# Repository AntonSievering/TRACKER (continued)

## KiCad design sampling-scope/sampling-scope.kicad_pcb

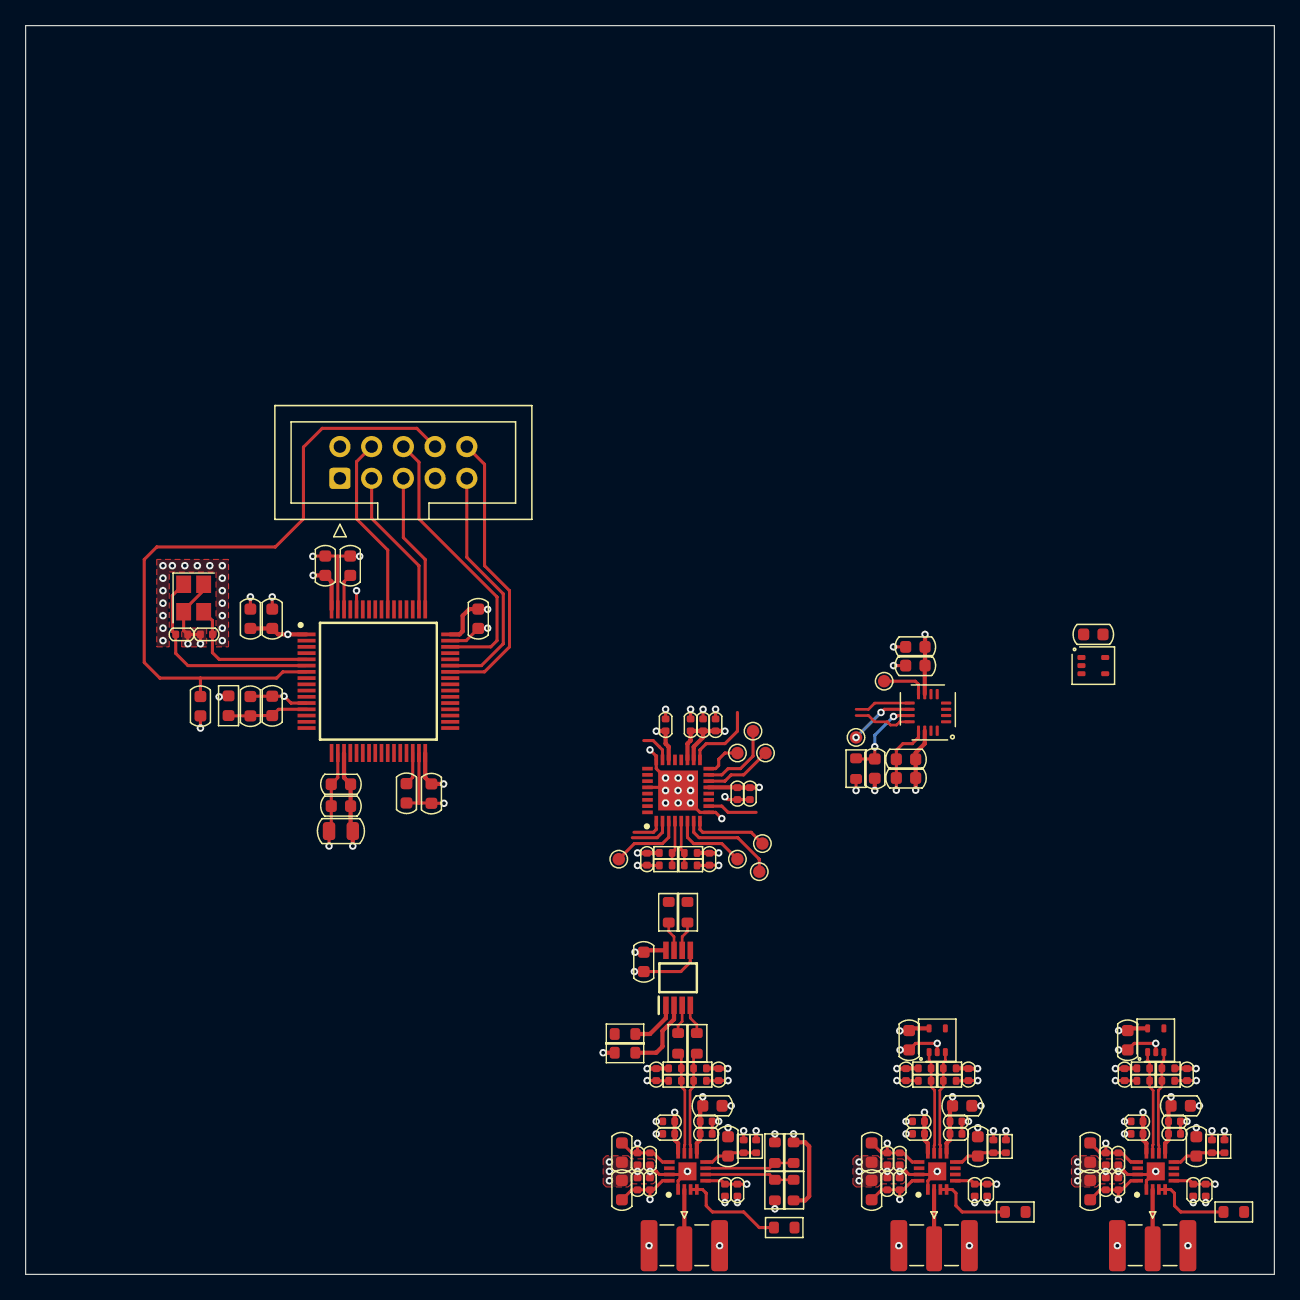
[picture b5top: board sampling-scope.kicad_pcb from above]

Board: 4 copper layers, 100.0 x 100.0 mm, 141 parts (0 on the bottom side), 53 nets.

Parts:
C1, C20, C21, C36, C37, C38, C39, C44, C45, C46, C47, C48, C49: 100n; C_0603_1608Metric
C2, C7, C8, C11, C12, C13, C14, C16, C18, C19, C24, C25, C26, C27, C29, C31, C32, C54, C55, C56, C57, C59, C61, C62, C63, C64, C65, C66, C67, C68, C69, C70, C71, C72, C73, C74, C75, C76, C77, C78: 100n; C_0402_1005Metric
C3, C4, C5, C6: 10n; C_0402_1005Metric
C9, C10, C15, C17, C22, C23, C28, C30, C43, C50, C51, C52, C53, C58, C60: 1u; C_0603_1608Metric
C33, C34, C35: 10n; C_0603_1608Metric
C40, C41: 2u2; C_0603_1608Metric
C42: 10u; C_0805_2012Metric
C79, C80: 10p; C_0402_1005Metric
FB1: 1k@100MHz; L_0603_1608Metric
IC1: SY89296UMG; QFN50P500X500X90-33N-D
IC2, IC4, IC6: ADCMP582; QFN50P300X300X80-17N-D
IC3: SY10EP51VKG; SOP65P490X110-8N
IC5: STM32H562RGT6; QFP50P1200X1200X160-64N
J1, J2, J3: SMA; SMA_Edge_Mount
J4: Conn_02x05_Counter_Clockwise; IDC-Header_2x05_P2.54mm_Vertical
R1, R3, R6, R8, R10, R21, R23, R25, R30, R32, R34: 127; R_0402_1005Metric
R2, R4, R7, R9, R11, R22, R24, R26, R31, R33, R35: 82.5; R_0402_1005Metric
R5, R14, R15, R16, R17, R18, R19, R20, R29, R37, R38: 0; R_0603_1608Metric
R27: 49R9; R_0603_1608Metric
R36: 470; R_0603_1608Metric
R39: 330; R_0603_1608Metric
TP1, TP4, TP5, TP6, TP7, TP8, TP9, TP10, TP11: TestPoint; TestPoint_Pad_D1.0mm
U1, U2, U4: LMV331; SOT-353_SC-70-5
U3: SY89831U; QFN-16_3x3mm_P0.5mm
X2: 40MHz; Crystal_SMD_Abracon_ABM8AIG-4Pin_3.2x2.5mm

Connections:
+3.3V: C1.1, C2.1, C3.1, C4.1, C5.1, C6.1, C7.1, C8.1, C15.1, C16.1, C18.1, C19.1, C20.1, C21.1, C28.1, C29.1, C31.1, C32.1, C33.1, C34.1, C35.1, C36.1, C37.1, C38.1, C42.1, C43.1, C44.1, C45.1, C46.1, C47.1, C48.1, C50.1, C58.1, C59.1, C61.1, C62.1, C69.1, C70.1, C71.1, C72.1, C73.1, C74.1, C75.1, C76.1, C77.1, C78.1, FB1.2, IC1.13 (VCC), IC1.18 (VCC), IC1.19 (VCC), IC1.22 (VCC), IC2.9 (V_{CCO}), IC2.12 (V_{CCO}), IC3.8 (VCC), IC4.9 (V_{CCO}), IC4.12 (V_{CCO}), IC5.1 (VBAT), IC5.19 (VDD_1), IC5.32 (VDD_2), IC5.48 (VDD_3), IC5.64 (VDD_4), IC6.9 (V_{CCO}), IC6.12 (V_{CCO}), R1.1, R3.1, R6.1, R8.1, R10.1, R15.1, R21.1, R23.1, R25.1, R30.1, R32.1, R34.1, R36.2, R38.2, U1.5 (V+), U2.5 (V+), U3.7 (VCC), U3.14 (VCC), U4.5 (V+)
+5VA: C10.1, C12.1, C14.1, C23.1, C25.1, C27.1, C53.1, C55.1, C57.1, C63.1, C64.1, C65.1, C66.1, C67.1, C68.1, IC2.5 (VCCI), IC2.16 (VCCI), IC4.5 (VCCI), IC4.16 (VCCI), IC6.5 (VCCI), IC6.16 (VCCI)
-5VA: C9.1, C11.1, C13.1, C22.1, C24.1, C26.1, C52.1, C54.1, C56.1, IC2.13 (V_{EE}), IC4.13 (V_{EE}), IC6.13 (V_{EE})
/Clock Fanout 1:4/IN+: IC1.20 (~Q), U3.12 (IN)
/Clock Fanout 1:4/IN-: IC1.21 (Q), U3.9 (~IN)
/Microcontroller/DEBUG_RX: IC5.43 (PA10), J4.9
/Microcontroller/DEBUG_TX: IC5.42 (PA9), J4.10
/Microcontroller/JTCK: IC5.49 (PA14), J4.5
/Microcontroller/JTDI: IC5.50 (PA15), J4.3
/Microcontroller/JTDO: IC5.55 (PB3), J4.4
/Microcontroller/JTMS: IC5.46 (PA13), J4.6
/Microcontroller/NRST: C39.1, IC5.7 (NRST), J4.8
/Microcontroller/OSC_IN: C79.2, IC5.5 (PH0-OSC_IN), X2.3
/Microcontroller/OSC_OUT: C80.2, IC5.6 (PH1-OSC_OUT), X2.1
/Microcontroller/stm32_vdda: C49.1, C51.1, FB1.1, IC5.13 (VDDA)
/Microcontroller/stm_vcap1: C40.1, IC5.30 (VCAP_1)
/Microcontroller/stm_vcap2: C41.1, IC5.62 (VCAP_2)
/Sampling Head CH1/High Speed Comparator/COMP_OUT+: IC4.11 (Q), R23.2, R24.1, U2.1 (+)
/Sampling Head CH1/High Speed Comparator/COMP_OUT-: IC4.10 (~Q), R25.2, R26.1, U2.3 (-)
/Sampling Head CH1/SIGNAL: IC4.2 (VP), J2.1 (In)
/Sampling Head CH2/High Speed Comparator/COMP_OUT+: IC6.11 (Q), R32.2, R33.1, U4.1 (+)
/Sampling Head CH2/High Speed Comparator/COMP_OUT-: IC6.10 (~Q), R34.2, R35.1, U4.3 (-)
/Sampling Head CH2/SIGNAL: IC6.2 (VP), J3.1 (In)
/Trigger Circuitry/High Speed Comparator/CMP_LE+: IC2.7 (LE), R36.1, R37.2
/Trigger Circuitry/High Speed Comparator/CMP_LE-: IC2.6 (~LE), R38.1, R39.2
/Trigger Circuitry/TRIG: IC2.2 (VP), J1.1 (In)
/Trigger Circuitry/comp_out+: IC2.11 (Q), R8.2, R9.1, R16.1
/Trigger Circuitry/comp_out-: IC2.10 (~Q), R10.2, R11.1, R17.1
/Trigger Circuitry/comp_out_r+: IC3.3 (CLK), R16.2
/Trigger Circuitry/comp_out_r-: IC3.4 (~CLK), R17.2
/Trigger Circuitry/dff_out+: IC3.7 (Q), R18.1
/Trigger Circuitry/dff_out-: IC3.6 (~Q), R19.1
/Trigger Circuitry/dff_out_r+: IC1.4 (IN), R1.2, R2.1, R18.2
/Trigger Circuitry/dff_out_r-: IC1.5 (~IN), R3.2, R4.1, R19.2
GND: C1.2, C2.2, C3.2, C4.2, C5.2, C6.2, C7.2, C8.2, C9.2, C10.2, C11.2, C12.2, C13.2, C14.2, C15.2, C16.2, C17.2, C18.2, C19.2, C20.2, C21.2, C22.2, C23.2, C24.2, C25.2, C26.2, C27.2, C28.2, C29.2, C30.2, C31.2, C32.2, C34.2, C35.2, C36.2, C37.2, C38.2, C39.2, C40.2, C41.2, C42.2, C43.2, C44.2, C45.2, C46.2, C47.2, C48.2, C49.2, C50.2, C51.2, C52.2, C53.2, C54.2, C55.2, C56.2, C57.2, C58.2, C59.2, C60.2, C61.2, C62.2, C63.2, C64.2, C65.2, C66.2, C67.2, C68.2, C69.2, C70.2, C71.2, C72.2, C73.2, C74.2, C75.2, C76.2, C77.2, C78.2, C79.1, C80.1, IC1.9 (GND), IC1.24 (GND), IC1.28 (GND), IC1.33 (EP), IC2.1 (VTP), IC2.15 (GND), IC2.17 (EP), IC3.5 (GND), IC4.1 (VTP), IC4.15 (GND), IC4.17 (EP), IC5.12 (VSSA), IC5.18 (VSS_1), IC5.31 (VSS_2), IC5.47 (VSS_3), IC5.60 (BOOT0), IC5.63 (VSS_4), IC6.1 (VTP), IC6.15 (GND), IC6.17 (EP), J1.2 (Ext), J2.2 (Ext), J3.2 (Ext), J4.2, J4.7, R2.2, R4.2, R7.2, R9.2, R11.2, R22.2, R24.2, R26.2, R27.2, R31.2, R33.2, R35.2, R37.1, R39.1, U1.2 (V-), U2.2 (V-), U3.13 (GND), U4.2 (V-), X2.2, X2.4
unnamed: IC1.15 (CASCADE), TP5.1
unnamed: IC1.3 (D10), TP1.1
unnamed: IC1.6 (VBB), TP9.1
unnamed: IC1.8 (VCF), TP7.1
unnamed: IC1.7 (VEF), TP8.1
unnamed: IC1.14 (~CASCADE), TP6.1
unnamed: IC1.16 (~EN), TP4.1
unnamed: IC2.3 (VN), IC2.4 (VTN), R5.2
unnamed: C17.1, IC2.8 (V_{TT}), R6.2, R7.1
unnamed: IC3.2 (D), R15.2
unnamed: IC3.1 (RESET), R14.2
unnamed: IC4.3 (VN), IC4.4 (VTN), R20.2
unnamed: C30.1, IC4.8 (V_{TT}), R21.2, R22.1
unnamed: IC6.3 (VN), IC6.4 (VTN), R29.2
unnamed: C60.1, IC6.8 (V_{TT}), R30.2, R31.1
unnamed: TP11.1, U3.8 (RESET)
unnamed: TP10.1, U3.10 (VREF-AC)
unnamed: C33.2, R27.1, U3.11 (VT)

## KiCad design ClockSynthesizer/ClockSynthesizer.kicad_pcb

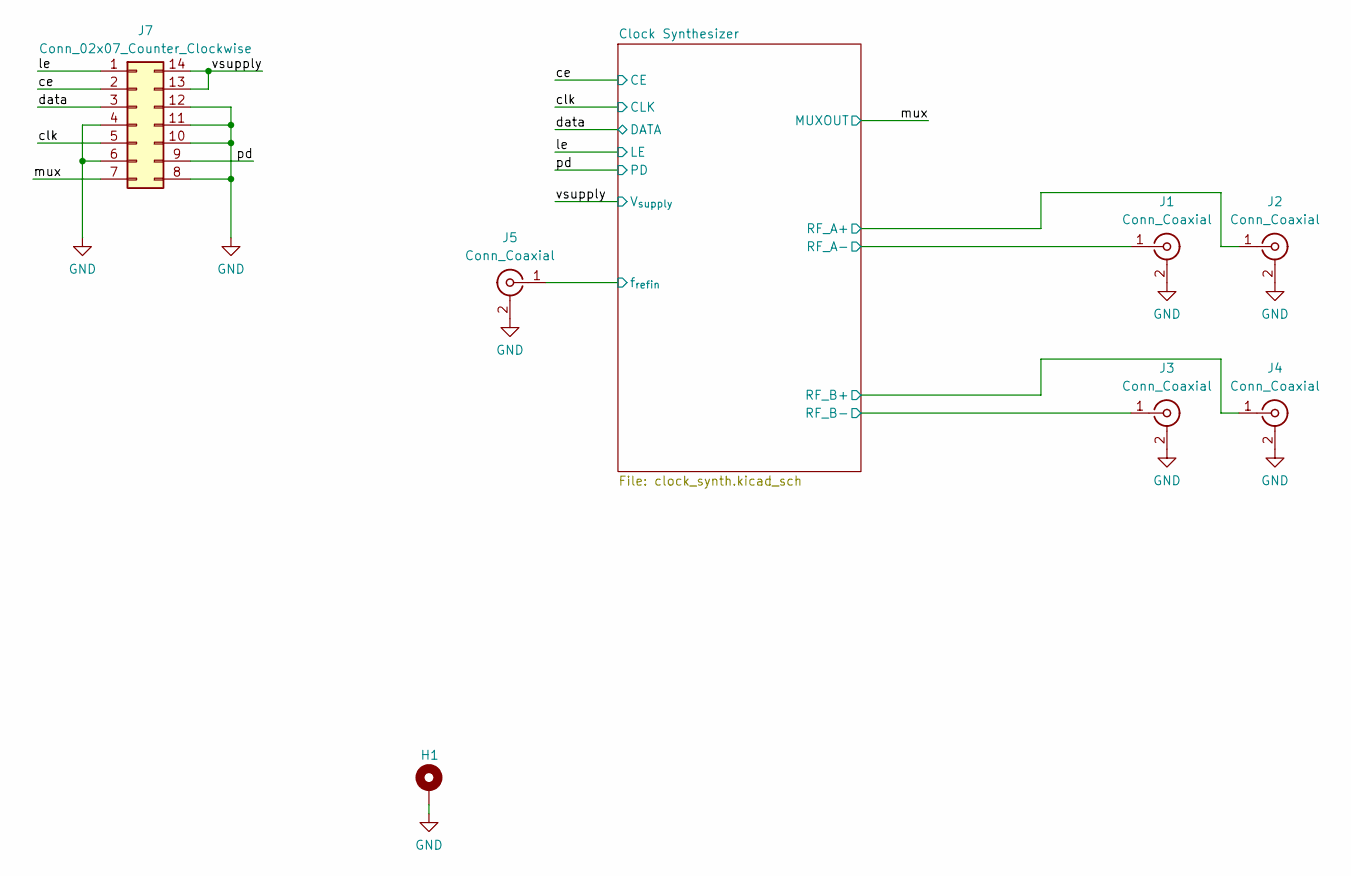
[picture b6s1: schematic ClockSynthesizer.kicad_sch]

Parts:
H1: MountingHole_Pad; MountingHole_3.2mm_M3_Pad_Via
J1, J2, J3, J4, J5: Conn_Coaxial; SMA_Amphenol_132289_EdgeMount
J7: Conn_02x07_Counter_Clockwise; PinHeader_2x07_P2.54mm_Horizontal

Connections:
+12V: J7.13, J7.14; also elsewhere on the board
/Clock Synthesizer/RF_A+: J2.1 (In); also elsewhere on the board
/Clock Synthesizer/RF_A-: J1.1 (In); also elsewhere on the board
/Clock Synthesizer/RF_B+: J4.1 (In); also elsewhere on the board
/Clock Synthesizer/RF_B-: J3.1 (In); also elsewhere on the board
/Clock Synthesizer/f_{refin}: J5.1 (In); also elsewhere on the board
/ce: J7.2; also elsewhere on the board
/clk: J7.5; also elsewhere on the board
/data: J7.3; also elsewhere on the board
/le: J7.1; also elsewhere on the board
/mux: J7.7; also elsewhere on the board
/pd: J7.9; also elsewhere on the board
GND: H1.1, J1.2 (Ext), J2.2 (Ext), J3.2 (Ext), J4.2 (Ext), J5.2 (Ext), J7.4, J7.6, J7.8, J7.10, J7.11, J7.12; also elsewhere on the board

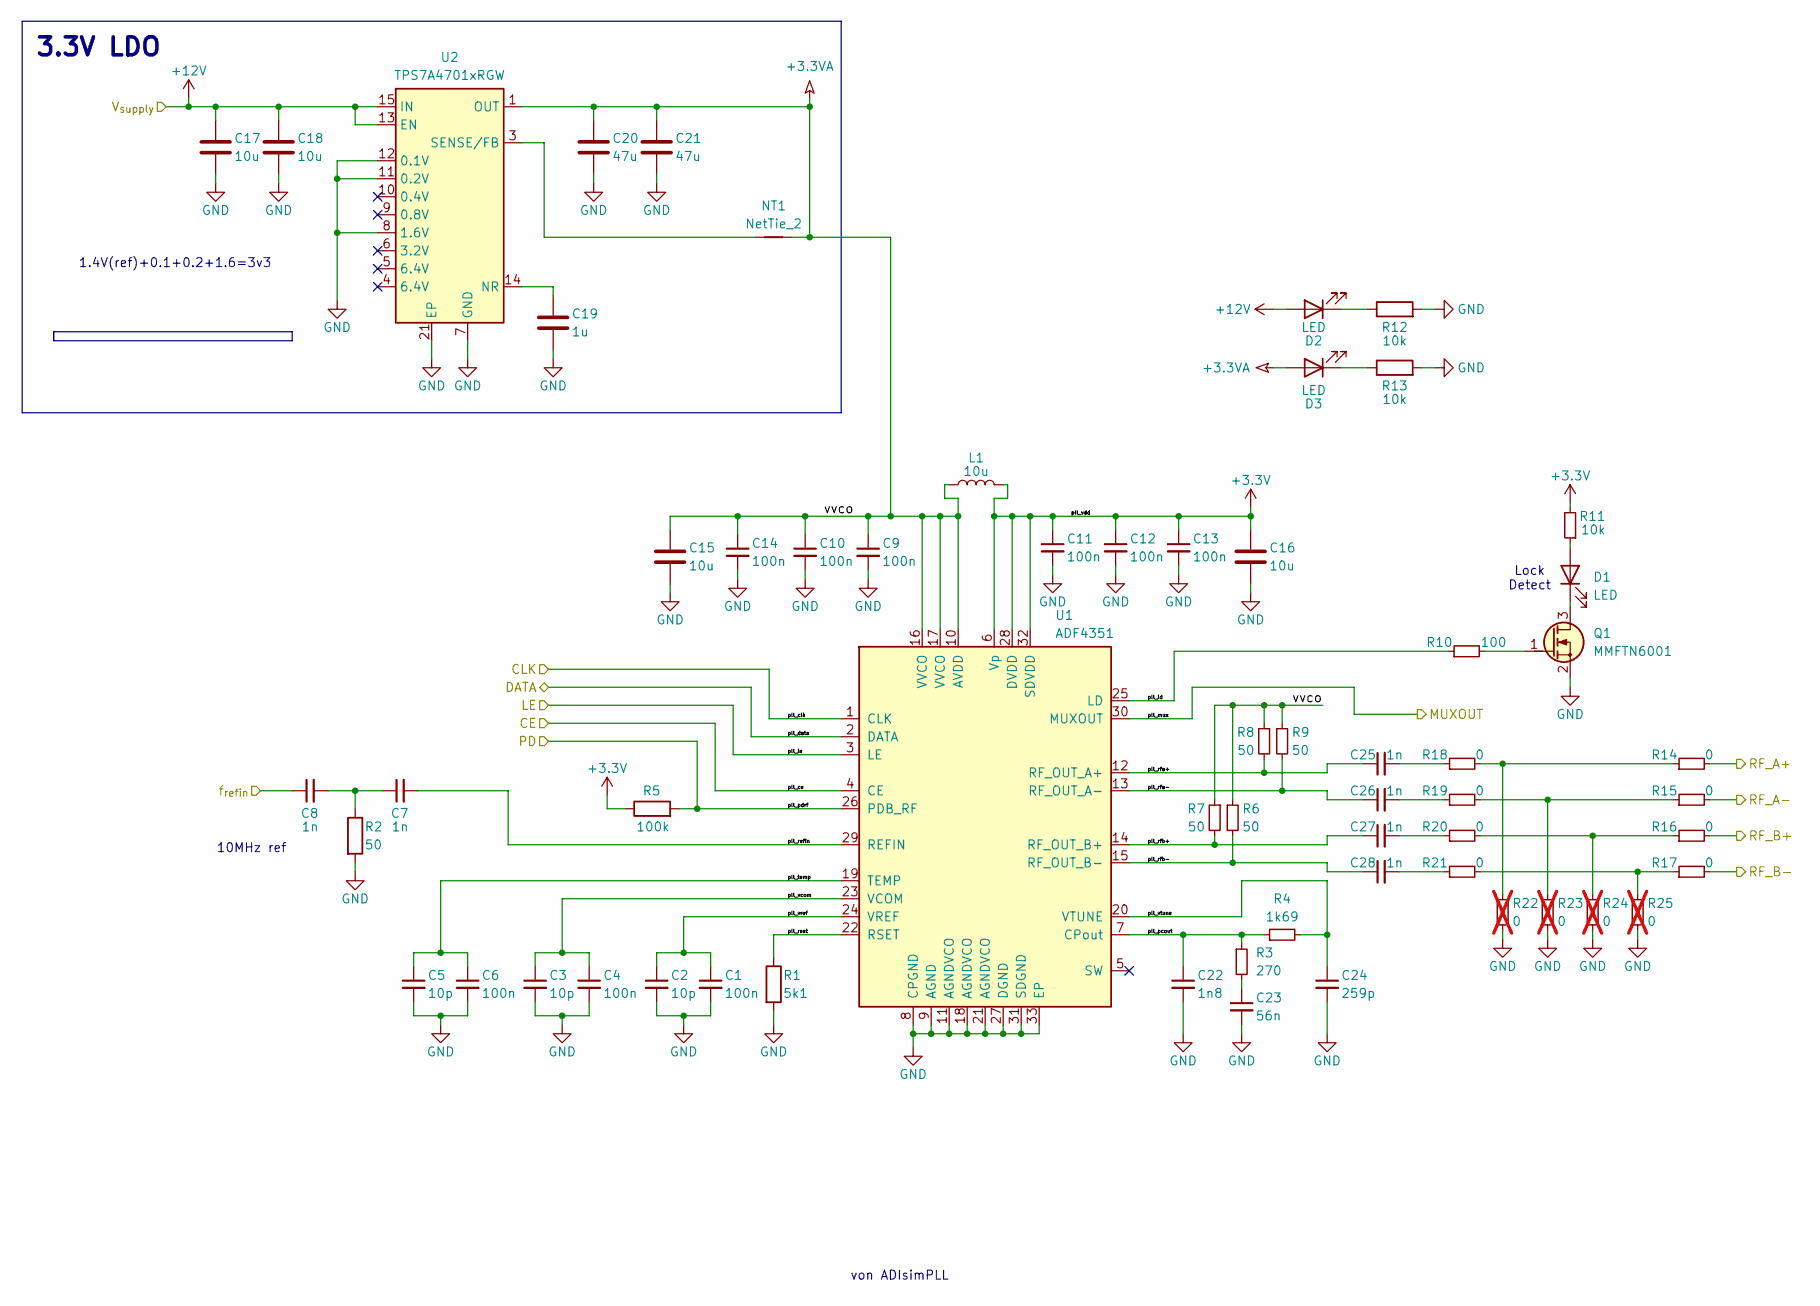
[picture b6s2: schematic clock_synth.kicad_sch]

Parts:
C1, C4, C6, C9, C10, C11, C12, C13, C14: 100n; C_0402_1005Metric; MPN 710-885012205086
C2, C3, C5: 10p; C_0402_1005Metric; MPN 963-UMK105UJ100DV-F
C7, C8, C25, C26, C27, C28: 1n; C_0402_1005Metric; MPN 581-04023C102KAZ2A
C15, C16, C17, C18: 10u; C_0805_2012Metric; MPN 963-LMK212BJ106KG-T
C19: 1u; C_0603_1608Metric
C20, C21: 47u; C_0805_2012Metric; MPN 81-GRM21BR61A476ME5L
C22: 1n8; C_0402_1005Metric; MPN 80-C0402C182K5RAUTO
C23: 56n; C_0402_1005Metric; MPN 81-GRM155R61A564ME5D
C24: 259p; C_0402_1005Metric; MPN 603-AC0402JNPO9BN271
D1, D2, D3: LED; D_0603_1608Metric
L1: 10u; L_0603_1608Metric; MPN 810-MLZ1608E100MT
NT1: NetTie_2; NetTie-2_SMD_Pad0.5mm
Q1: MMFTN6001; SOT-23; MPN 637-MMFTN6001
R1: 5k1; R_0402_1005Metric; MPN 603-AC0402JR-075K1L
R2, R6, R7, R8, R9: 50; R_0402_1005Metric; MPN 603-RT0402BRE0750RL
R3: 270; R_0402_1005Metric; MPN 652-CR0402-JW-271GLF
R4: 1k69; R_0402_1005Metric; MPN 652-CR0402-FX1691GLF
R5: 100k; R_0402_1005Metric; MPN 71-RCG0402100KJNED
R10: 100; R_0402_1005Metric; MPN 603-RC0402JR-7D100RL
R11, R12, R13: 10k; R_0603_1608Metric
R14, R15, R16, R17, R18, R19, R20, R21: 0; R_0402_1005Metric; MPN 652-CR0402-J/-000GLF
R22, R23, R24, R25: 0; R_0402_1005Metric; not fitted
U1: ADF4351; LFCSP-32-1EP_5x5mm_P0.5mm_EP3.25x3.25mm; MPN 584-ADF4351BCPZ-R7
U2: TPS7A4701xRGW; Texas_RGW0020A_VQFN-20-1EP_5x5mm_P0.65mm_EP3.15x3.15mm_Ther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; MPN 595-TPS7A4700RGWR

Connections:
+3.3V: C11.1, C12.1, C13.1, C16.1, L1.2, R5.1, R11.2, U1.6 (Vp), U1.28 (DVDD), U1.32 (SDVDD)
+3.3VA: C9.1, C10.1, C14.1, C15.1, C20.1, C21.1, D3.2 (A), L1.1, NT1.2, R6.1, R7.1, R8.1, R9.1, U1.10 (AVDD), U1.16 (VVCO), U1.17 (VVCO), U2.1 (OUT), U2.20 (OUT)
+12V: C17.1, C18.1, D2.2 (A), U2.13 (EN), U2.15 (IN), U2.16 (IN); also elsewhere on the board
/Clock Synthesizer/RF_A+: R14.2; also elsewhere on the board
/Clock Synthesizer/RF_A-: R15.2; also elsewhere on the board
/Clock Synthesizer/RF_B+: R16.2; also elsewhere on the board
/Clock Synthesizer/RF_B-: R17.2; also elsewhere on the board
/Clock Synthesizer/f_{refin}: C8.1; also elsewhere on the board
/Clock Synthesizer/pll_ld: R10.1, U1.25 (LD)
/Clock Synthesizer/pll_pcout: C22.1, R3.1, R4.1, U1.7 (CPout)
/Clock Synthesizer/pll_refin: C7.2, U1.29 (REFIN)
/Clock Synthesizer/pll_rfa+: C25.1, R8.2, U1.12 (RF_OUT_A+)
/Clock Synthesizer/pll_rfa-: C26.1, R9.2, U1.13 (RF_OUT_A-)
/Clock Synthesizer/pll_rfb+: C27.1, R7.2, U1.14 (RF_OUT_B+)
/Clock Synthesizer/pll_rfb-: C28.1, R6.2, U1.15 (RF_OUT_B-)
/Clock Synthesizer/pll_rset: R1.1, U1.22 (RSET)
/Clock Synthesizer/pll_temp: C5.1, C6.1, U1.19 (TEMP)
/Clock Synthesizer/pll_vcom: C3.1, C4.1, U1.23 (VCOM)
/Clock Synthesizer/pll_vref: C1.1, C2.1, U1.24 (VREF)
/Clock Synthesizer/pll_vtune: C24.1, R4.2, U1.20 (VTUNE)
/ce: U1.4 (CE); also elsewhere on the board
/clk: U1.1 (CLK); also elsewhere on the board
/data: U1.2 (DATA); also elsewhere on the board
/le: U1.3 (LE); also elsewhere on the board
/mux: U1.30 (MUXOUT); also elsewhere on the board
/pd: R5.2, U1.26 (PDB_RF); also elsewhere on the board
GND: C1.2, C2.2, C3.2, C4.2, C5.2, C6.2, C9.2, C10.2, C11.2, C12.2, C13.2, C14.2, C15.2, C16.2, C17.2, C18.2, C19.2, C20.2, C21.2, C22.2, C23.2, C24.2, Q1.2 (S), R1.2, R2.2, R12.2, R13.2, R22.2, R23.2, R24.2, R25.2, U1.8 (CPGND), U1.9 (AGND), U1.11 (AGNDVCO), U1.18 (AGNDVCO), U1.21 (AGNDVCO), U1.27 (DGND), U1.31 (SDGND), U1.33 (EP), U2.7 (GND), U2.8 (1.6V), U2.11 (0.2V), U2.12 (0.1V), U2.21 (EP); also elsewhere on the board
unnamed: C7.1, C8.2, R2.1
unnamed: C23.1, R3.2
unnamed: C25.2, R18.1
unnamed: C26.2, R19.1
unnamed: C27.2, R20.1
unnamed: C28.2, R21.1
unnamed: D1.2 (A), R11.1
unnamed: D1.1 (K), Q1.3 (D)
unnamed: D2.1 (K), R12.1
unnamed: D3.1 (K), R13.1
unnamed: Q1.1 (G), R10.2
unnamed: R14.1, R18.2, R22.1
unnamed: R15.1, R19.2, R23.1
unnamed: R16.1, R20.2, R24.1
unnamed: R17.1, R21.2, R25.1
unnamed: C19.1, U2.14 (NR)
unnamed: NT1.1, U2.3 (SENSE/FB)

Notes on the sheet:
3.3V LDO
von ADIsimPLL
Lock Detect
1.4V(ref)+0.1+0.2+1.6=3v3
10MHz ref

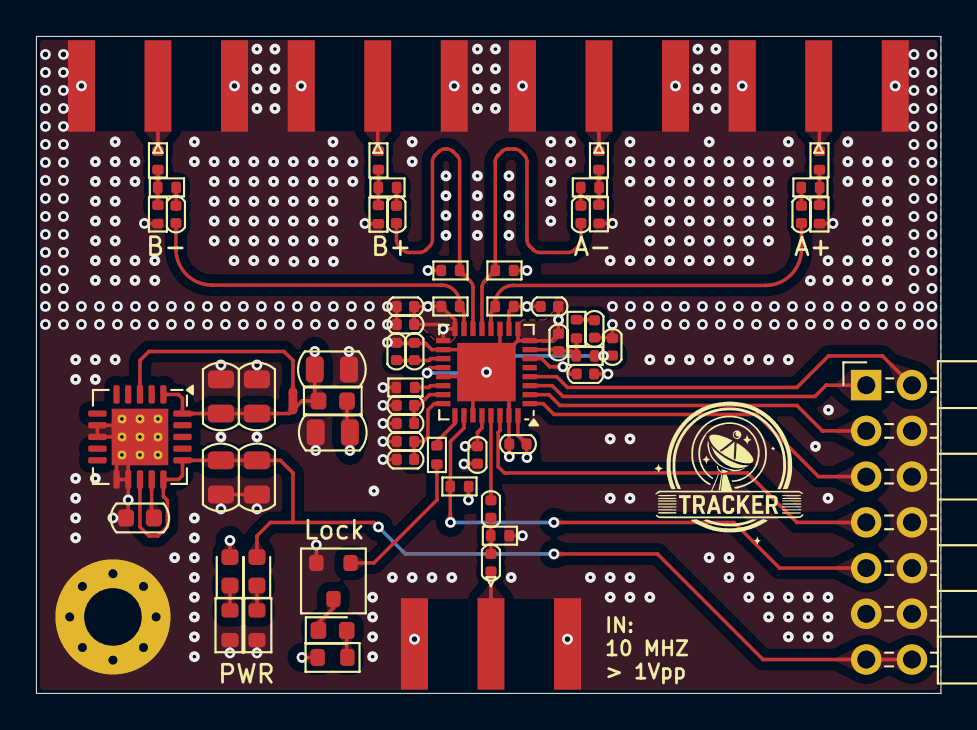
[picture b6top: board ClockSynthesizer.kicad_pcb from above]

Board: 4 copper layers, 50.2 x 36.5 mm, 68 parts (0 on the bottom side), 44 nets.

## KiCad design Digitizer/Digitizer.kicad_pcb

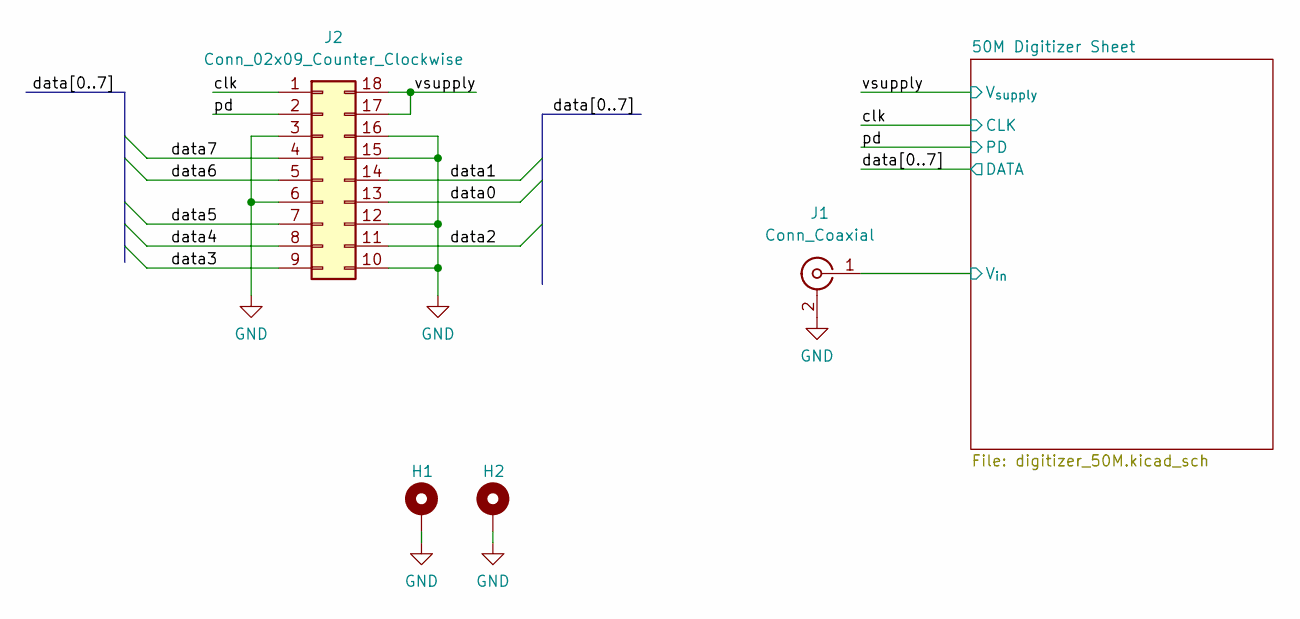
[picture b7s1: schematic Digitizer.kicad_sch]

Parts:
H1, H2: MountingHole_Pad; MountingHole_3.2mm_M3_Pad_Via
J1: Conn_Coaxial; SMA_Amphenol_132289_EdgeMount
J2: Conn_02x09_Counter_Clockwise; PinHeader_2x09_P2.54mm_Horizontal

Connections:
+12V: J2.17, J2.18; also elsewhere on the board
/50M Digitizer Sheet/V_{in}: J1.1 (In); also elsewhere on the board
/clk: J2.1; also elsewhere on the board
/data0: J2.13; also elsewhere on the board
/data1: J2.14; also elsewhere on the board
/data2: J2.11; also elsewhere on the board
/data3: J2.9; also elsewhere on the board
/data4: J2.8; also elsewhere on the board
/data5: J2.7; also elsewhere on the board
/data6: J2.5; also elsewhere on the board
/data7: J2.4; also elsewhere on the board
/pd: J2.2; also elsewhere on the board
GND: H1.1, H2.1, J1.2 (Ext), J2.3, J2.6, J2.10, J2.12, J2.15, J2.16; also elsewhere on the board

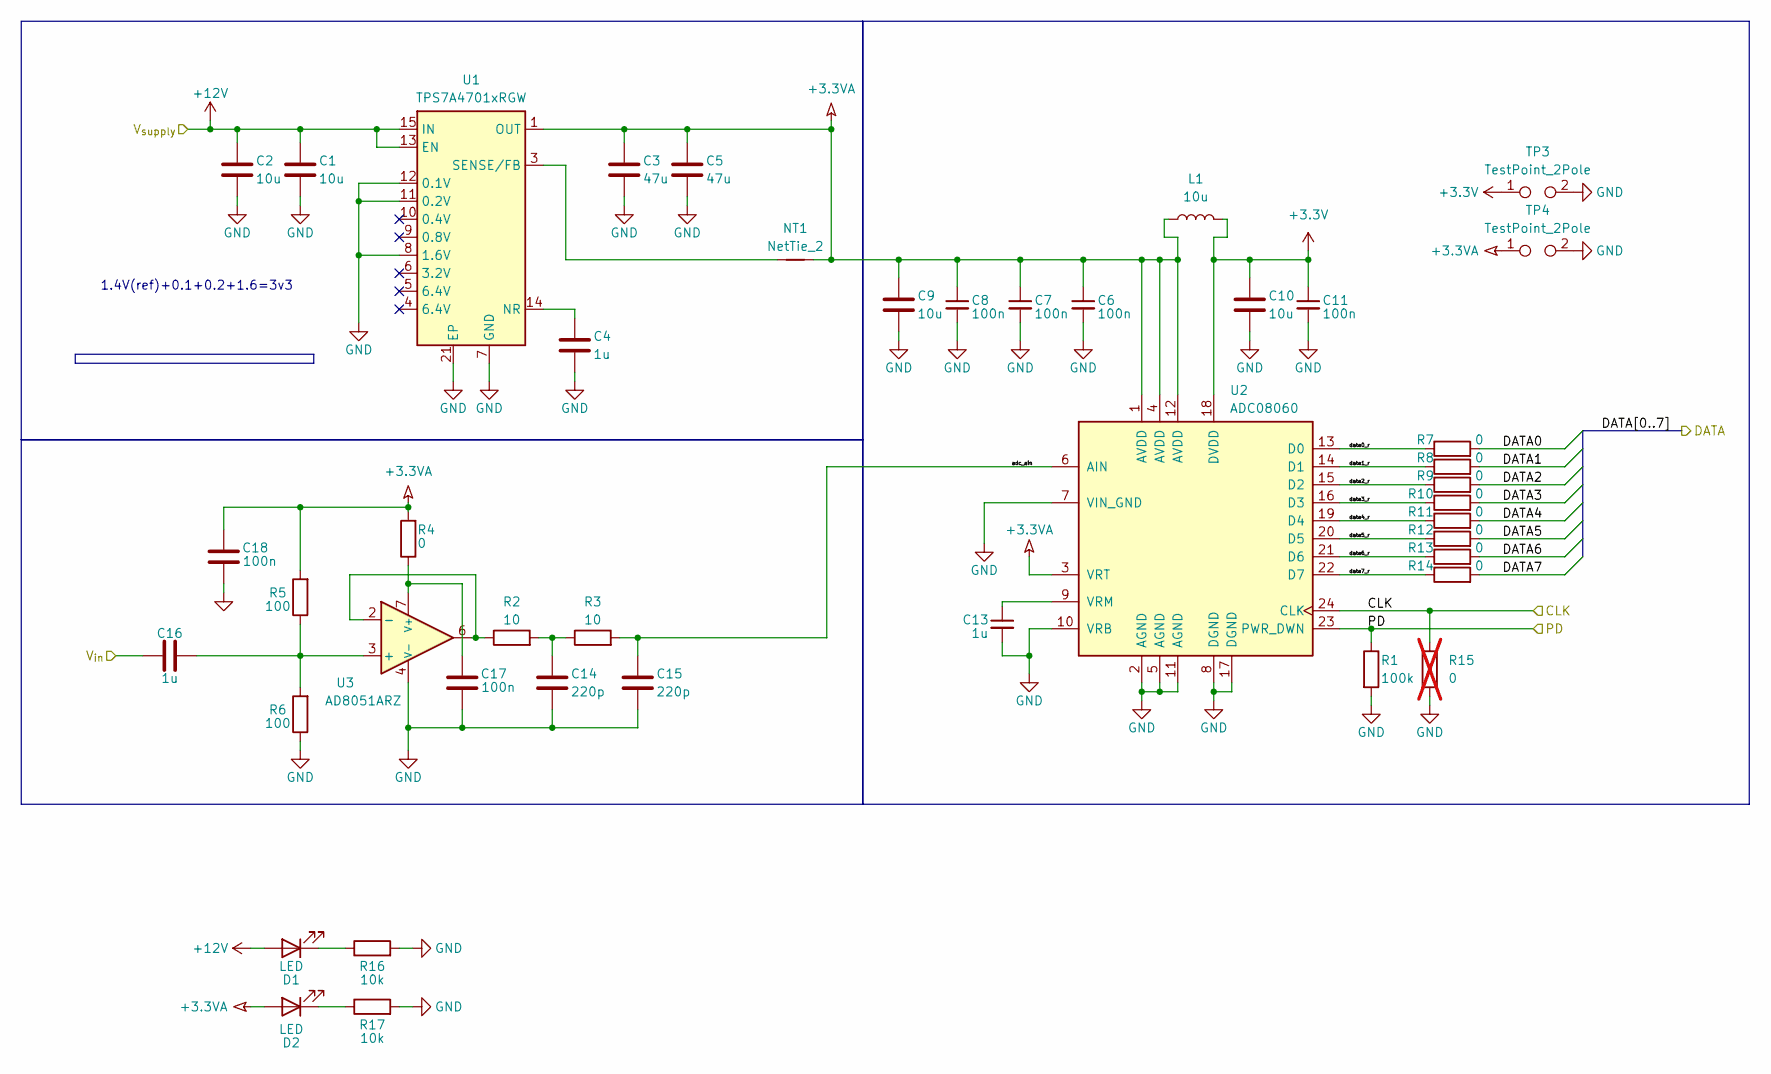
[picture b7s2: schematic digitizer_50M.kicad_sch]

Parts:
C1, C2, C9, C10: 10u; C_0805_2012Metric
C3, C5: 47u; C_0805_2012Metric; MPN 81-GRM21BR61A476ME5L
C4, C13, C16: 1u; C_0603_1608Metric
C6, C7, C8, C11, C17, C18: 100n; C_0603_1608Metric
C14, C15: 220p; C_0603_1608Metric
D1, D2: LED; D_0603_1608Metric
L1: 10u; L_0603_1608Metric; MPN 810-MLZ1608E100MT
NT1: NetTie_2; NetTie-2_SMD_Pad0.5mm
R1: 100k; R_0603_1608Metric
R2, R3: 10; R_0603_1608Metric
R4, R7, R8, R9, R10, R11, R12, R13, R14: 0; R_0603_1608Metric
R5, R6: 100; R_0603_1608Metric
R15: 0; R_0603_1608Metric; not fitted
R16, R17: 10k; R_0603_1608Metric
TP3, TP4: TestPoint_2Pole; TestPoint_2Pads_Pitch2.54mm_Drill0.8mm
U1: TPS7A4701xRGW; Texas_RGW0020A_VQFN-20-1EP_5x5mm_P0.65mm_EP3.15x3.15mm_Ther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; MPN 595-TPS7A4700RGWR
U2: ADC08060; TSSOP-24_4.4x7.8mm_P0.65mm; MPN 926-ADC08060CIMTXNPB
U3: AD8051ARZ; SO-8_3.9x4.9mm_P1.27mm; MPN 584-AD8051ARZ-R7

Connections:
+3.3V: C10.1, C11.1, L1.2, TP3.1, U2.18 (DVDD)
+3.3VA: C3.1, C5.1, C6.1, C7.1, C8.1, C9.1, C18.2, D2.2 (A), L1.1, NT1.2, R4.2, R5.2, TP4.1, U1.1 (OUT), U1.20 (OUT), U2.1 (AVDD), U2.3 (VRT), U2.4 (AVDD), U2.12 (AVDD)
+12V: C1.1, C2.1, D1.2 (A), U1.13 (EN), U1.15 (IN), U1.16 (IN); also elsewhere on the board
/50M Digitizer Sheet/V_{in}: C16.1; also elsewhere on the board
/50M Digitizer Sheet/adc_ain: C15.1, R3.2, U2.6 (AIN)
/50M Digitizer Sheet/data0_r: R7.1, U2.13 (D0)
/50M Digitizer Sheet/data1_r: R8.1, U2.14 (D1)
/50M Digitizer Sheet/data2_r: R9.1, U2.15 (D2)
/50M Digitizer Sheet/data3_r: R10.1, U2.16 (D3)
/50M Digitizer Sheet/data4_r: R11.1, U2.19 (D4)
/50M Digitizer Sheet/data5_r: R12.1, U2.20 (D5)
/50M Digitizer Sheet/data6_r: R13.1, U2.21 (D6)
/50M Digitizer Sheet/data7_r: R14.1, U2.22 (D7)
/clk: R15.1, U2.24 (CLK); also elsewhere on the board
/data0: R7.2; also elsewhere on the board
/data1: R8.2; also elsewhere on the board
/data2: R9.2; also elsewhere on the board
/data3: R10.2; also elsewhere on the board
/data4: R11.2; also elsewhere on the board
/data5: R12.2; also elsewhere on the board
/data6: R13.2; also elsewhere on the board
/data7: R14.2; also elsewhere on the board
/pd: R1.1, U2.23 (PWR_DWN); also elsewhere on the board
GND: C1.2, C2.2, C3.2, C4.2, C5.2, C6.2, C7.2, C8.2, C9.2, C10.2, C11.2, C13.2, C14.2, C15.2, C17.1, C18.1, R1.2, R6.1, R15.2, R16.2, R17.2, TP3.2, TP4.2, U1.7 (GND), U1.8 (1.6V), U1.11 (0.2V), U1.12 (0.1V), U1.21 (EP), U2.2 (AGND), U2.5 (AGND), U2.7 (VIN_GND), U2.8 (DGND), U2.10 (VRB), U2.11 (AGND), U2.17 (DGND), U3.4 (V-); also elsewhere on the board
unnamed: C14.1, R2.2, R3.1
unnamed: D1.1 (K), R16.1
unnamed: D2.1 (K), R17.1
unnamed: C4.1, U1.14 (NR)
unnamed: NT1.1, U1.3 (SENSE/FB)
unnamed: C13.1, U2.9 (VRM)
unnamed: C16.2, R5.1, R6.2, U3.3 (+)
unnamed: R2.1, U3.2 (-), U3.6
unnamed: C17.2, R4.1, U3.7 (V+)

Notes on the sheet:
1.4V(ref)+0.1+0.2+1.6=3v3

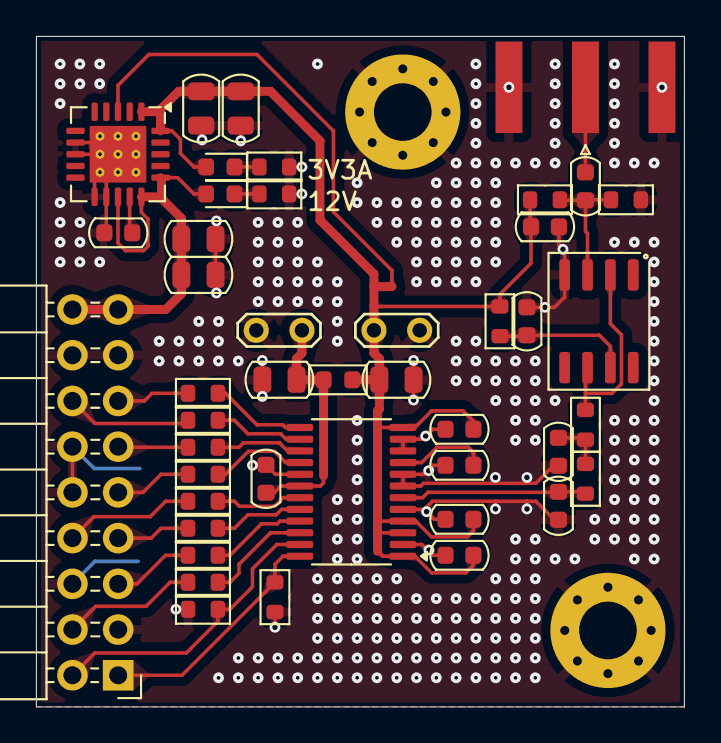
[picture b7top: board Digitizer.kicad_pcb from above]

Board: 2 copper layers, 36.0 x 37.2 mm, 47 parts (0 on the bottom side), 33 nets.

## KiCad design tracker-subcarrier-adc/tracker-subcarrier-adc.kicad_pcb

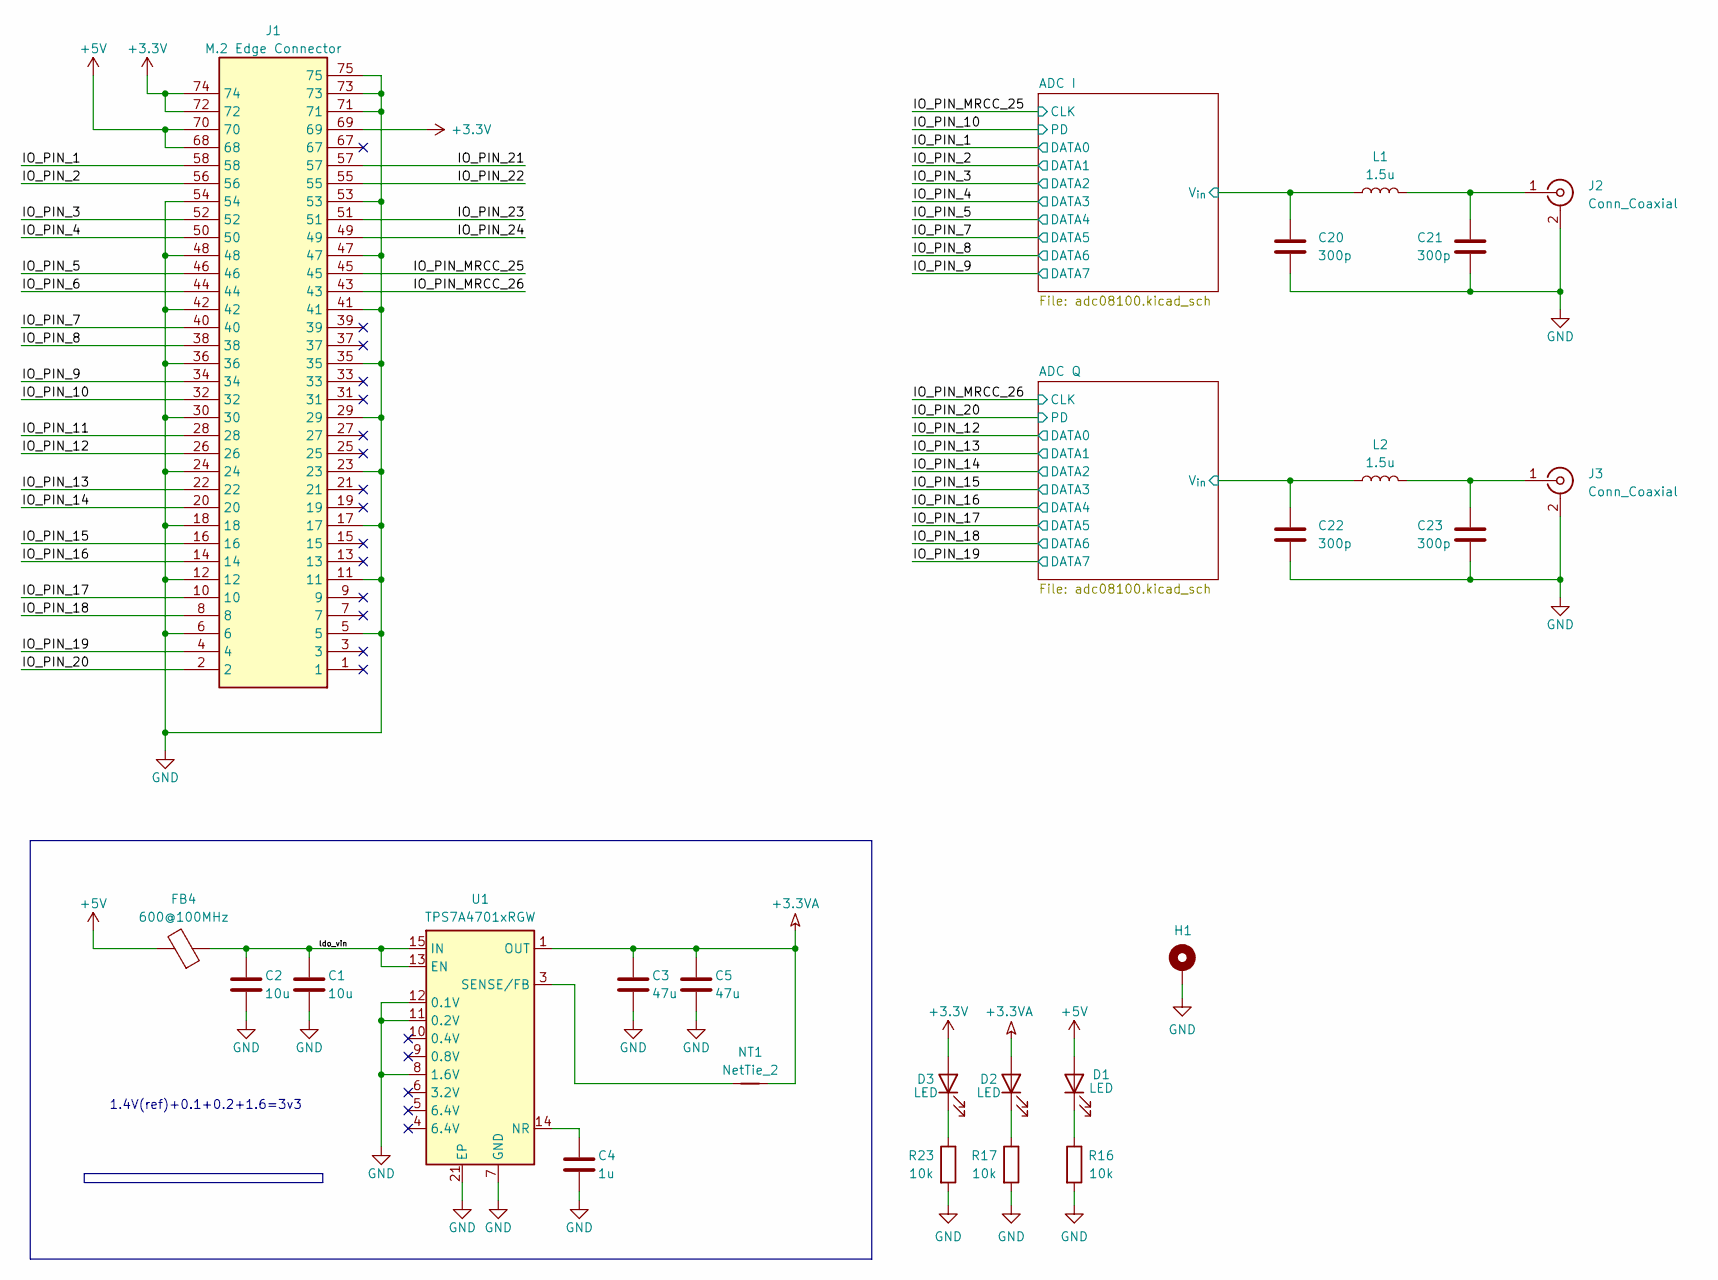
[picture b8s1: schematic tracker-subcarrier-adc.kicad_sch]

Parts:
C1, C2: 10u; C_0805_2012Metric
C3, C5: 47u; C_0805_2012Metric; MPN 81-GRM21BR61A476ME5L
C4: 1u; C_0603_1608Metric
C20, C21, C22, C23: 300p; C_0603_1608Metric; MPN GCM1885C2A301FA16J
D1, D2, D3: LED; D_0603_1608Metric
FB4: 600@100MHz; L_0805_2012Metric
H1: MountingHole_Pad; MountingHole_2.5mm_Pad
J1: M.2 Edge Connector; M.2_2242-xx-M
J2, J3: Conn_Coaxial; SMA_Edge_Mount
L1, L2: 1.5u; L_0603_1608Metric; MPN MLF1608A1R5JT000
NT1: NetTie_2; NetTie-2_SMD_Pad0.5mm
R16, R17, R23: 10k; R_0603_1608Metric
U1: TPS7A4701xRGW; Texas_RGW0020A_VQFN-20-1EP_5x5mm_P0.65mm_EP3.15x3.15mm_Ther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; MPN 595-TPS7A4700RGWR

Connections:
+3.3V: D3.2 (A), J1.69, J1.72, J1.74; also elsewhere on the board
+3.3VA: C3.1, C5.1, D2.2 (A), NT1.2, U1.1 (OUT), U1.20 (OUT); also elsewhere on the board
+5V: D1.2 (A), FB4.2, J1.68, J1.70
/ADC I/adc_ain: C20.1, L1.1; also elsewhere on the board
/ADC Q/adc_ain: C22.1, L2.1; also elsewhere on the board
/IO_PIN_1: J1.58; also elsewhere on the board
/IO_PIN_2: J1.56; also elsewhere on the board
/IO_PIN_3: J1.52; also elsewhere on the board
/IO_PIN_4: J1.50; also elsewhere on the board
/IO_PIN_5: J1.46; also elsewhere on the board
/IO_PIN_6: J1.44
/IO_PIN_7: J1.40; also elsewhere on the board
/IO_PIN_8: J1.38; also elsewhere on the board
/IO_PIN_9: J1.34; also elsewhere on the board
/IO_PIN_10: J1.32; also elsewhere on the board
/IO_PIN_11: J1.28
/IO_PIN_12: J1.26; also elsewhere on the board
/IO_PIN_13: J1.22; also elsewhere on the board
/IO_PIN_14: J1.20; also elsewhere on the board
/IO_PIN_15: J1.16; also elsewhere on the board
/IO_PIN_16: J1.14; also elsewhere on the board
/IO_PIN_17: J1.10; also elsewhere on the board
/IO_PIN_18: J1.8; also elsewhere on the board
/IO_PIN_19: J1.4; also elsewhere on the board
/IO_PIN_20: J1.2; also elsewhere on the board
/IO_PIN_21: J1.57
/IO_PIN_22: J1.55
/IO_PIN_23: J1.51
/IO_PIN_24: J1.49
/IO_PIN_MRCC_25: J1.45; also elsewhere on the board
/IO_PIN_MRCC_26: J1.43; also elsewhere on the board
/ldo_vin: C1.1, C2.1, FB4.1, U1.13 (EN), U1.15 (IN), U1.16 (IN)
GND: C1.2, C2.2, C3.2, C4.2, C5.2, C20.2, C21.2, C22.2, C23.2, H1.1, J1.5, J1.6, J1.11, J1.12, J1.17, J1.18, J1.23, J1.24, J1.29, J1.30, J1.35, J1.36, J1.41, J1.42, J1.47, J1.48, J1.53, J1.54, J1.71, J1.73, J1.75, J2.2 (Ext), J3.2 (Ext), R16.2, R17.2, R23.2, U1.7 (GND), U1.8 (1.6V), U1.11 (0.2V), U1.12 (0.1V), U1.21 (EP); also elsewhere on the board
unnamed: D1.1 (K), R16.1
unnamed: D2.1 (K), R17.1
unnamed: D3.1 (K), R23.1
unnamed: C21.1, J2.1 (In), L1.2
unnamed: C23.1, J3.1 (In), L2.2
unnamed: C4.1, U1.14 (NR)
unnamed: NT1.1, U1.3 (SENSE/FB)

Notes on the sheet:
1.4V(ref)+0.1+0.2+1.6=3v3
